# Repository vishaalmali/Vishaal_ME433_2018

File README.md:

# Vishaal_ME433_2018
A collection of homeworks and files for ME433 Spring Quarter 2018.

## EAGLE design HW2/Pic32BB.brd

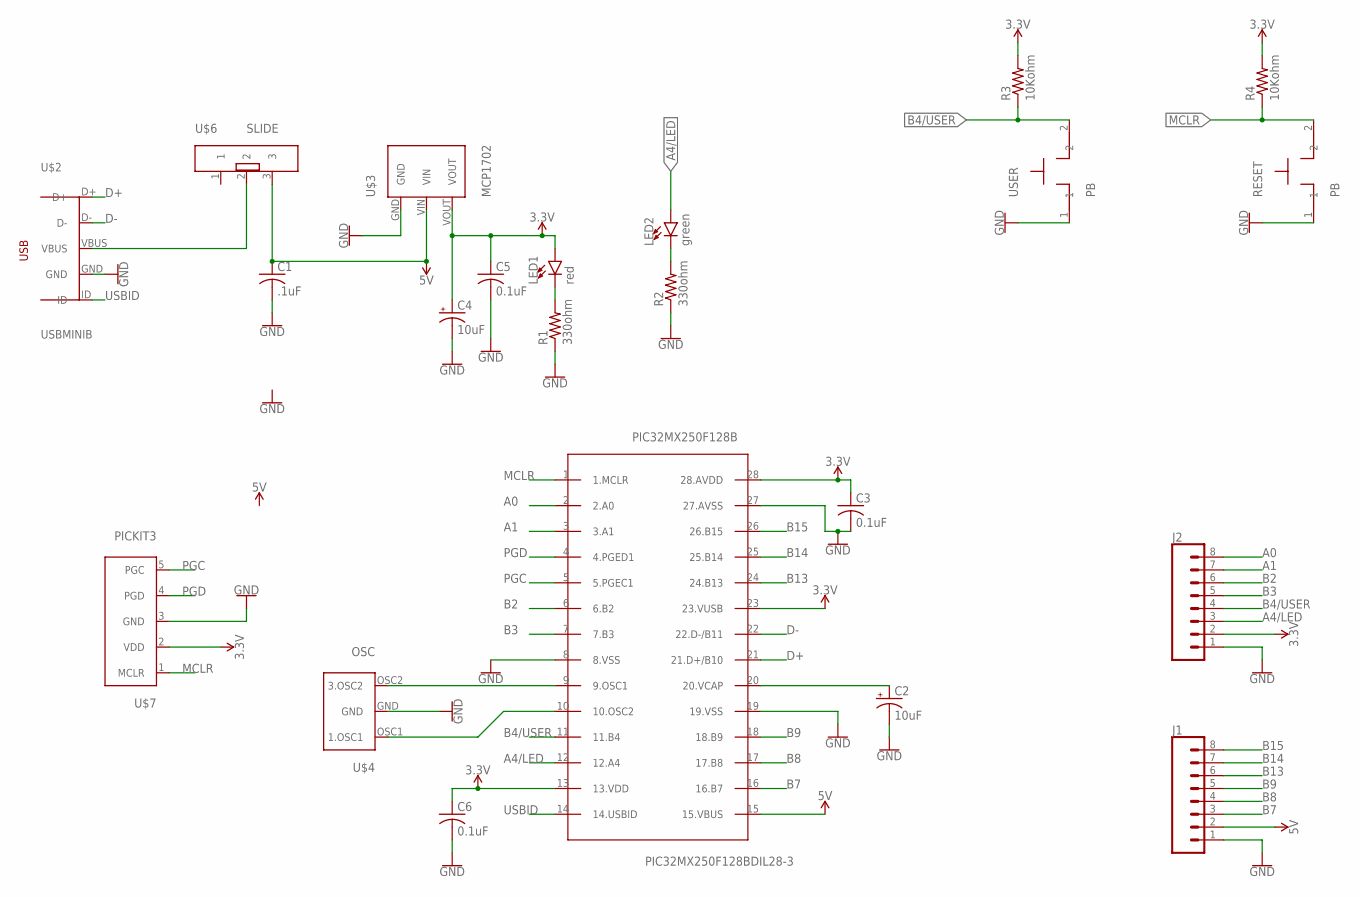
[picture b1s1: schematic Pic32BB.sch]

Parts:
C1: .1uF; C025-025X050
C2, C4: 10uF; B45181B
C3, C5, C6: 0.1uF; C025-025X050
J1, J2: CONN_08"; 1X08
LED1: red; LED_3MM
LED2: green; LED_3MM
PIC32MX250F128B: PIC32MX250F128BDIL28-3; DIL28-3
R1, R2: 330ohm; 0207/10
R3, R4: 10Kohm; 0207/10
RESET: PB
U$2: USBMINIB; USB-MB-H
U$3: MCP1702; TO92
U$4: OSC
U$6: SLIDE
U$7: PICKIT3
USER: PB

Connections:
3.3V: C3.1, C4.+, C5.1, C6.1, J2.2, LED1.A, PIC32MX250F128B.13 (13.VDD), PIC32MX250F128B.23 (23.VUSB), PIC32MX250F128B.28 (28.AVDD), R3.2, R4.2, U$3.VOUT, U$7.2 (VDD)
5V: C1.1, J1.2, PIC32MX250F128B.15 (15.VBUS), U$3.VIN, U$6.3
A0: J2.8, PIC32MX250F128B.2 (2.A0)
A1: J2.7, PIC32MX250F128B.3 (3.A1)
A4/LED: J2.3, LED2.A, PIC32MX250F128B.12 (12.A4)
B2: J2.6, PIC32MX250F128B.6 (6.B2)
B3: J2.5, PIC32MX250F128B.7 (7.B3)
B4/USER: J2.4, PIC32MX250F128B.11 (11.B4), R3.1, USER.2
B7: J1.3, PIC32MX250F128B.16 (16.B7)
B8: J1.4, PIC32MX250F128B.17 (17.B8)
B9: J1.5, PIC32MX250F128B.18 (18.B9)
B13: J1.6, PIC32MX250F128B.24 (24.B13)
B14: J1.7, PIC32MX250F128B.25 (25.B14)
B15: J1.8, PIC32MX250F128B.26 (26.B15)
D+: PIC32MX250F128B.21 (21.D+/B10), U$2.D+
D-: PIC32MX250F128B.22 (22.D-/B11), U$2.D-
GND: C1.2, C2.-, C3.2, C4.-, C5.2, C6.2, J1.1, J2.1, PIC32MX250F128B.8 (8.VSS), PIC32MX250F128B.19 (19.VSS), PIC32MX250F128B.27 (27.AVSS), R1.1, R2.1, RESET.1, U$2.GND, U$3.GND, U$4.GND, U$7.3 (GND), USER.1
MCLR: PIC32MX250F128B.1 (1.MCLR), R4.1, RESET.2, U$7.1 (MCLR)
unnamed: PIC32MX250F128B.9 (9.OSC1), U$4.OSC2 (3.OSC2)
unnamed: PIC32MX250F128B.10 (10.OSC2), U$4.OSC1 (1.OSC1)
unnamed: C2.+, PIC32MX250F128B.20 (20.VCAP)
unnamed: U$2.VBUS, U$6.2
unnamed: LED1.K (C), R1.2
unnamed: LED2.K (C), R2.2
PGC: PIC32MX250F128B.5 (5.PGEC1), U$7.5 (PGC)
PGD: PIC32MX250F128B.4 (4.PGED1), U$7.4 (PGD)
USBID: PIC32MX250F128B.14 (14.USBID), U$2.ID

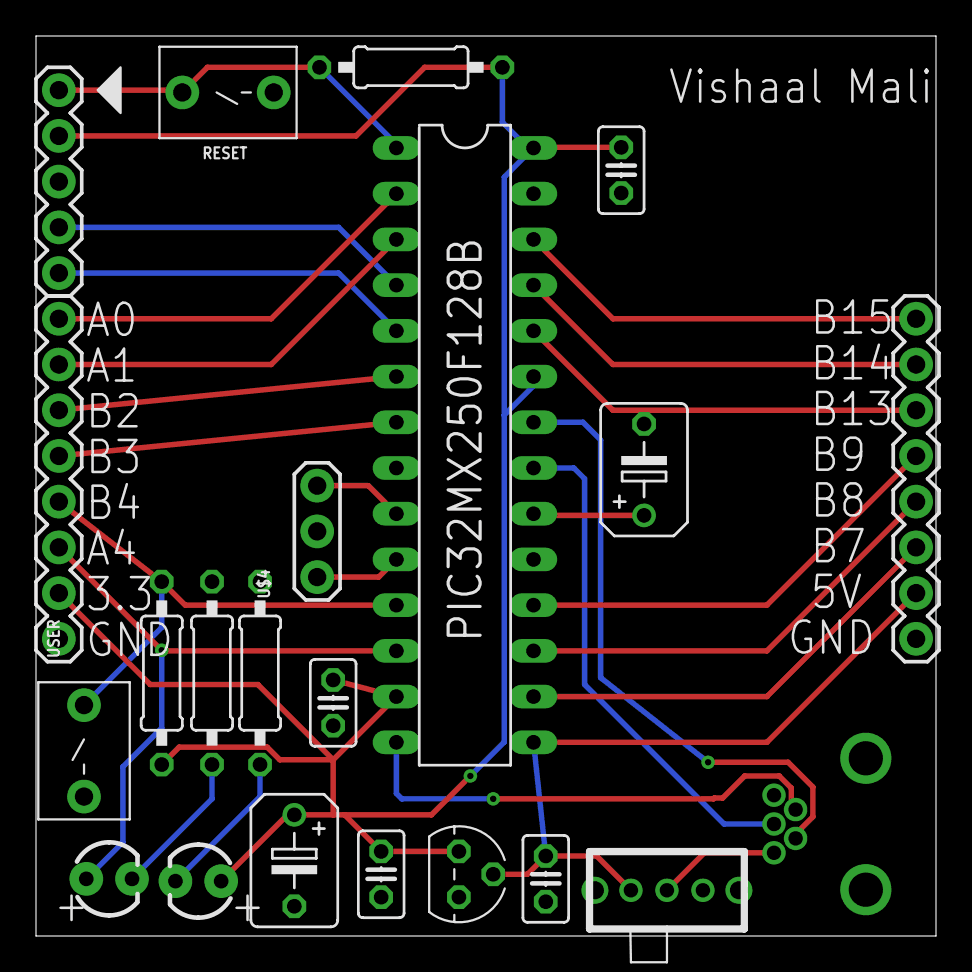
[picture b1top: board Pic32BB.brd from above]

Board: 2 copper layers, 50.0 x 50.0 mm, 22 parts (0 on the bottom side), 27 nets.

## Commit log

2018-04-10 HW1
    Added TRIS and LAT statements
2018-04-10 HW1
    Finished coding LED blinkning task
2018-04-10 HW1
    All requirements for HW1 are completed.
2018-04-17 HW2 schematic upload
2018-04-17 HW Pic32 breakout upload
2018-04-17 Gerber Files
    Zipped and uploaded the Gerber files.
2018-04-17 Images for HW1
2018-04-18 HW4
    Began the process of coding SPI protocol with DAC and pic32
2018-04-18 HW4
    Added declarations of ports that will be used for SPI protocol
2018-04-19 HW4
    Began writing the set voltage function for the SPI protocol.
2018-05-07 HW4
    Got SPI working fully, just need to implement sine and square waves.
2018-05-08 HW4
    Writing sin wave function
2018-05-08 HW4
    Both the sin wave and triangle wave functions are completed.
2018-05-08 DAC Osc Output
    Uploaded the image of the DAC output via the nscope oscilliscope.
2018-05-09 HW6
    Initial upload with starter code.
2018-05-10 HW6
    Wrote functions for writing string to LCD screen and writing chars to screen.
2018-05-26 HW6
    Progress bar code written
2018-05-26 HW12
    Finished building a basic Android App with sliding bar and text.
2018-05-26 HW12
    Uploaded video of demo.
2018-06-05 HW8
    Recreated HW1 using Harmony wizard in MPLAB.
2018-06-06 HW6
    Completed LCD code with fps, progress bar, and text.
2018-06-12 HW13
    Uploaded and completed the green detection code for the android camera.
2018-06-12 HW9
    Got the CDC code working and communicating with my computer.
2018-06-13 HW14
    Tested and completed HW14
2018-06-13 HW14 PIC CODE
    Finished USB for PIC 32.
2018-06-13 HW14
    merged pic and android hw 14 folders.
2018-06-17 ME433 Assignments
2018-06-17 TechCup final code and images
2018-06-17 HW5 upload
2018-06-17 HW7 Upload
2018-06-17 HW10 Upload
2018-06-17 HW11 upload

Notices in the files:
parts and their libraries:
SparkFun-Connectors: Licensing: Creative Commons ShareAlike 4.0 International - https://creativecommons.org/licenses/by-sa/4.0
